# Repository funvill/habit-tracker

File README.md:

# Every DayCalendar - Single Month board - KiCad

A single month habit tracker inspired by [Simone Giertz “The Every Day Calendar”](https://www.kickstarter.com/projects/simonegiertz/the-every-day-calendar). Allows for tracking of stats for multiple activities throughout the year. On each day, click the buttons for the activities that you have accomplished and the corresponding date on the calendar will illuminate with RGB LEDs.

- Months will progress automatically.
- Several different "modes"
- Physical buttons with leads to be able to expand on the board out to a frame.
- Ability to connect the boards together

Uses a ESP32 to connect to the internet and backup the data from the boards.

Fabricated using JLPCB SMD placement services. Fully automated manufacturing.

More information about this project can be found on my blog [project page](https://blog.abluestar.com/projects/2022-monthly-habit-tracker/)

See [changelog](changelog.md) for full list of changes

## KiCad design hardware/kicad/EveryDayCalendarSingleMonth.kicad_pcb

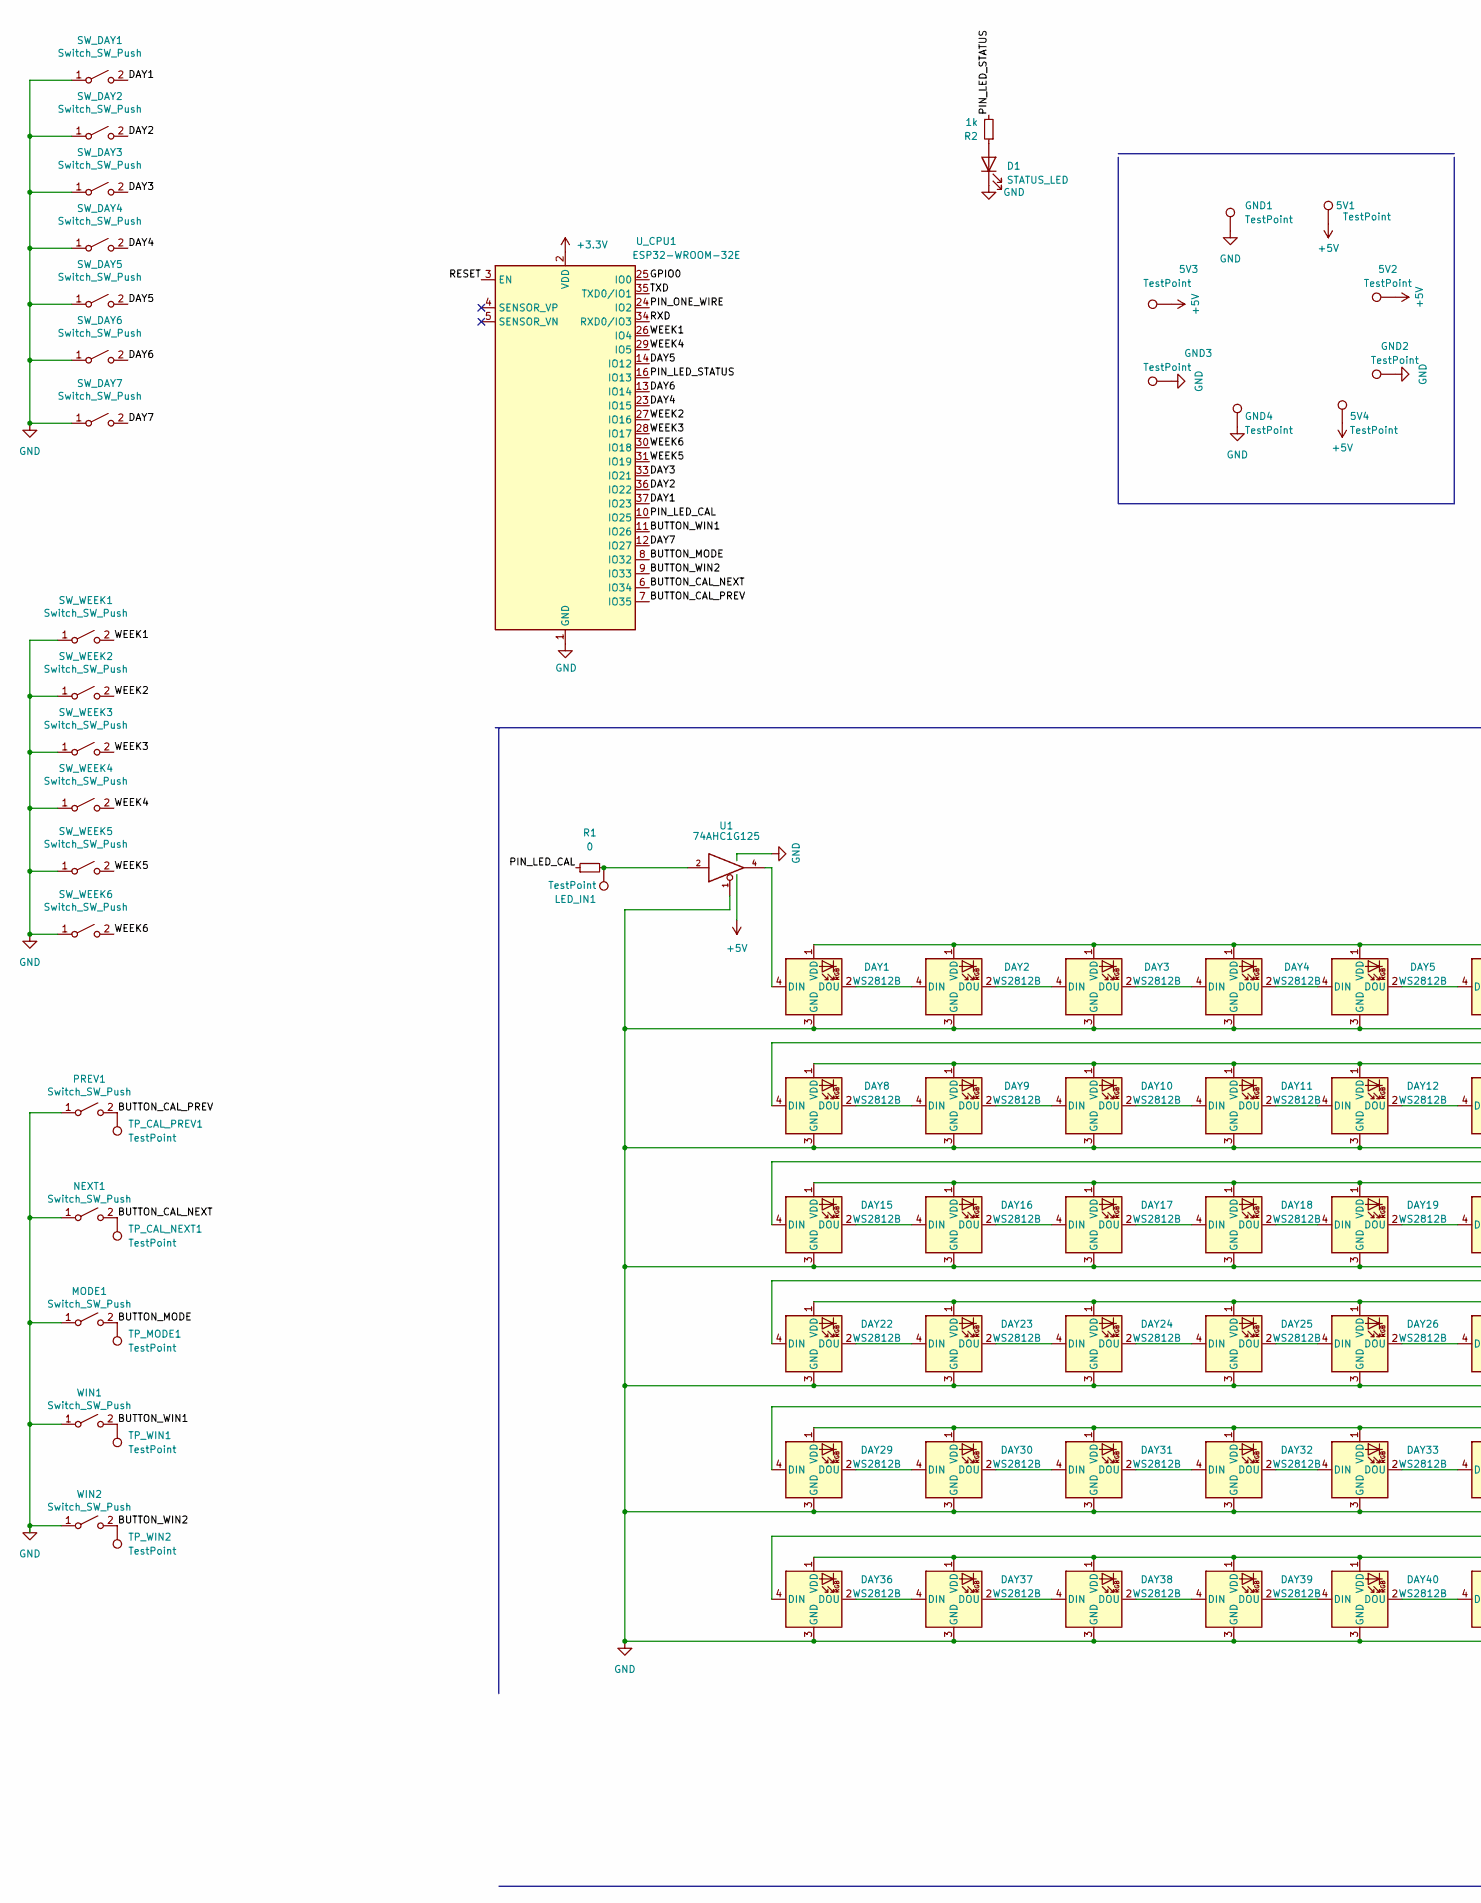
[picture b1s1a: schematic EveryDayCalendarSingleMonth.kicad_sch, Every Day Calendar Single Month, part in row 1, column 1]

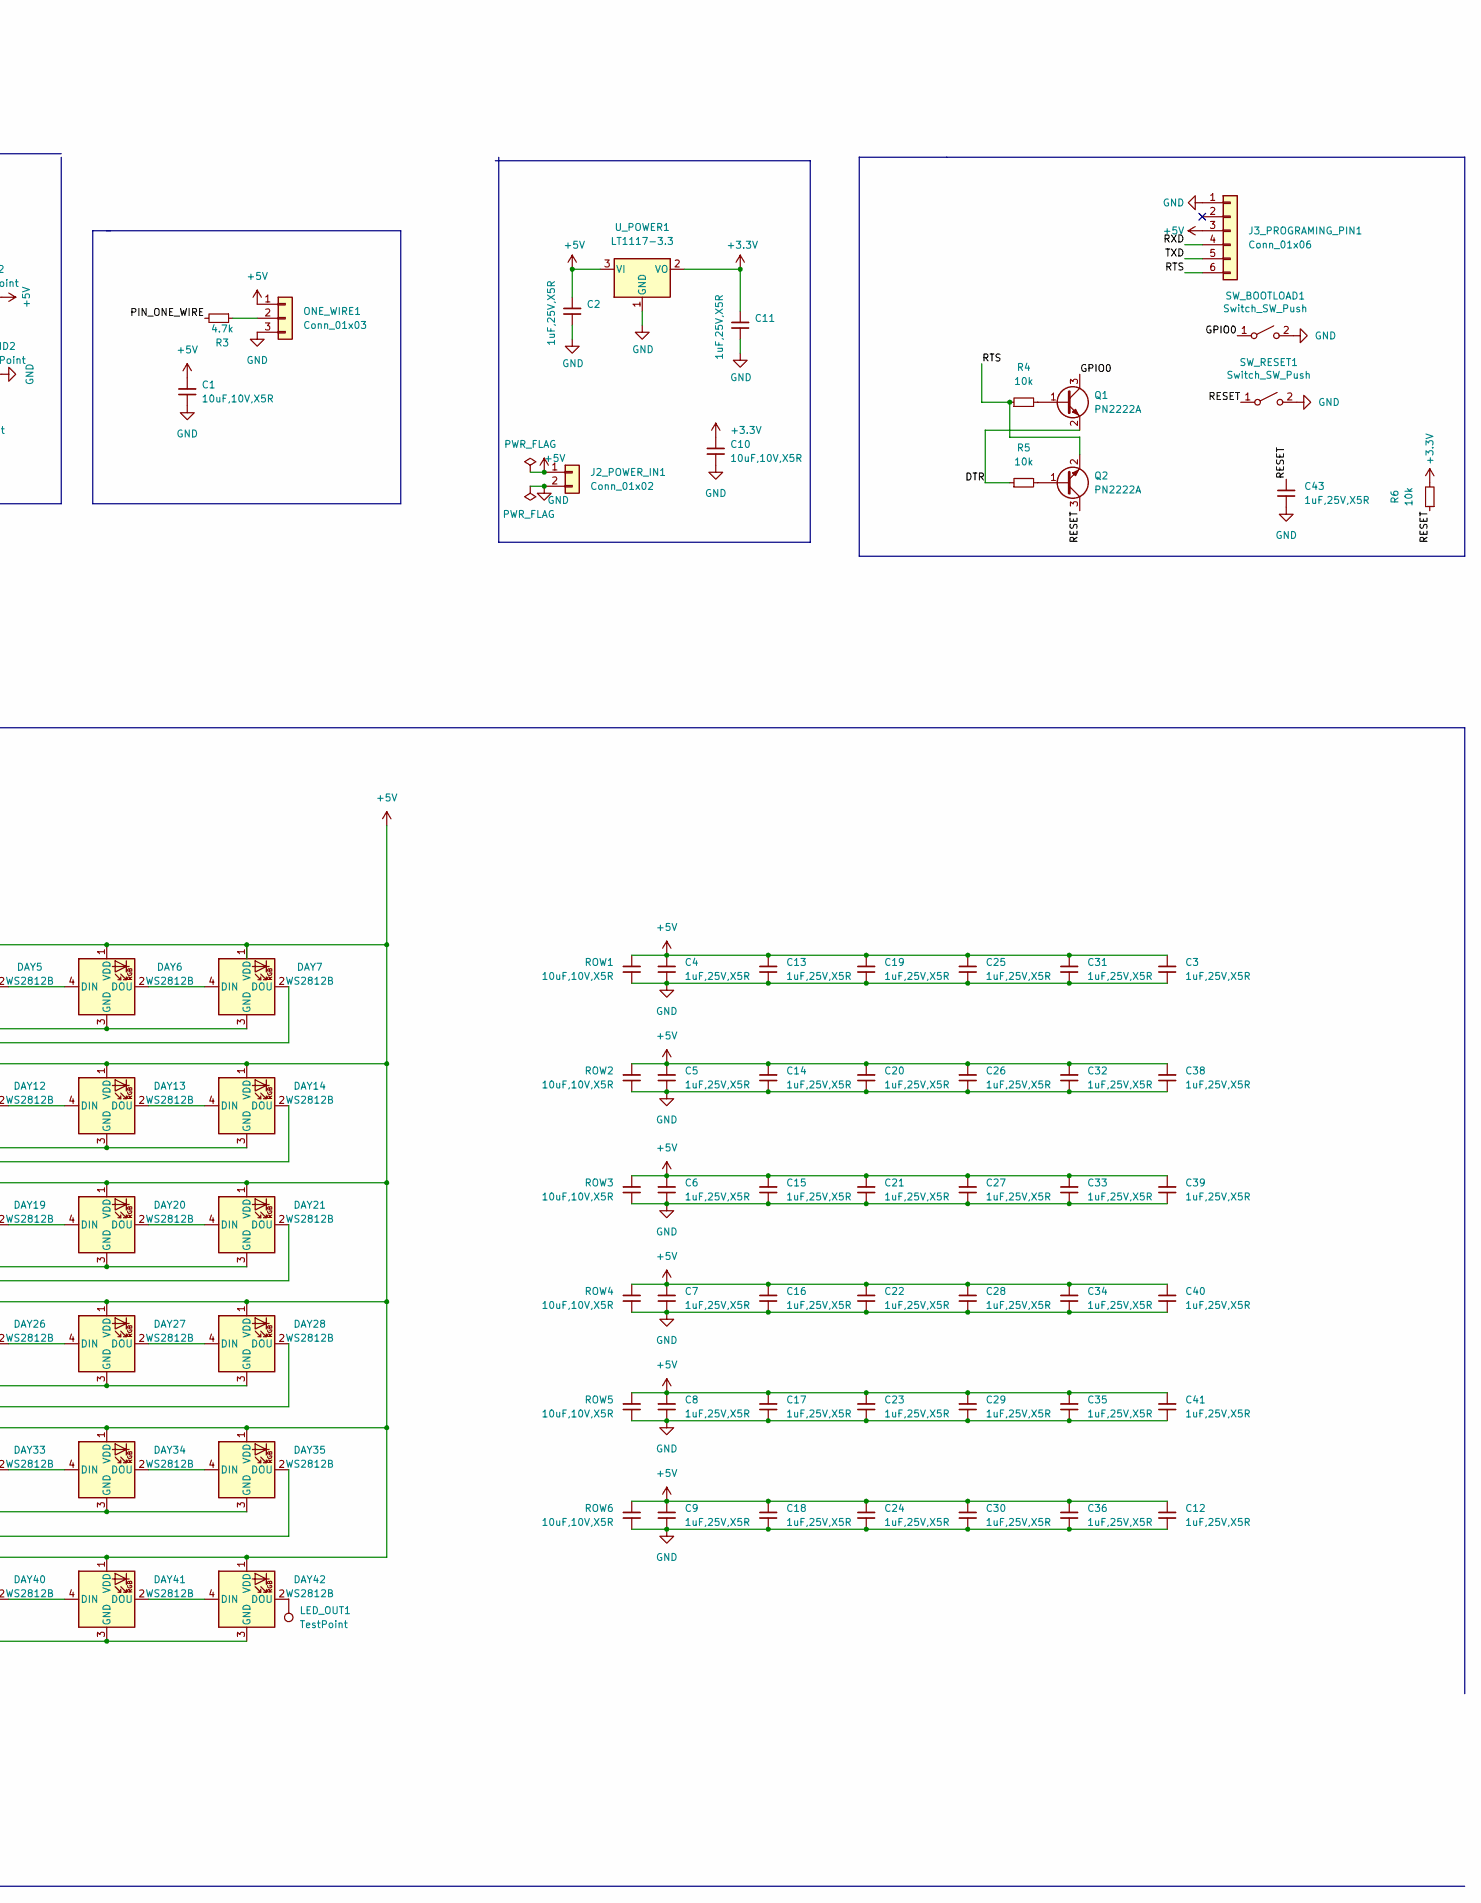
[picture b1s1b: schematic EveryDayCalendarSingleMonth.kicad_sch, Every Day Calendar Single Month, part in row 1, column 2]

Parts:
5V1, 5V2, 5V3, 5V4: TestPoint; TestPoint_Pad_2.5x2.5mm
C1, C10: 10uF,10V,X5R; C_0603_1608Metric; MFGPN CL10A106KP8NNNC; LCSC C19702
C2, C3, C4, C5, C6, C7, C8, C9, C11, C12, C13, C14, C15, C16, C17, C18, C19, C20, C21, C22, C23, C24, C25, C26, C27, C28, C29, C30, C31, C32, C33, C34, C35, C36, C38, C39, C40, C41, C43: 1uF,25V,X5R; C_0402_1005Metric; MFGPN CL05A105KA5NQNC; LCSC C52923
D1: STATUS_LED; LED_0603_1608Metric; LCSC C2286
DAY1, DAY2, DAY3, DAY4, DAY5, DAY6, DAY7, DAY8, DAY9, DAY10, DAY11, DAY12, DAY13, DAY14, DAY15, DAY16, DAY17, DAY18, DAY19, DAY20, DAY21, DAY22, DAY23, DAY24, DAY25, DAY26, DAY27, DAY28, DAY29, DAY30, DAY31, DAY32, DAY33, DAY34, DAY35, DAY36, DAY37, DAY38, DAY39, DAY40, DAY41, DAY42: WS2812B; LED_WS2812B_PLCC4_5.0x5.0mm_P3.2mm; LCSC C2843785
GND1, GND2, GND3, GND4: TestPoint; TestPoint_Pad_2.5x2.5mm
J2_POWER_IN1: Conn_01x02; PhoenixContact_MCV_1,5_2-G-3.81_1x02_P3.81mm_Vertical
J3_PROGRAMING_PIN1: Conn_01x06; PinHeader_1x06_P2.54mm_Vertical
LED_IN1: TestPoint; TestPoint_Pad_2.5x2.5mm
LED_OUT1: TestPoint; TestPoint_Pad_2.5x2.5mm
MODE1: Switch_SW_Push; SW_Push_1P1T_NO_6x6mm_H9.5mm; LCSC C221880
NEXT1: Switch_SW_Push; SW_Push_1P1T_NO_6x6mm_H9.5mm; LCSC C221880
ONE_WIRE1: Conn_01x03; PinHeader_1x03_P2.54mm_Vertical
PREV1: Switch_SW_Push; SW_Push_1P1T_NO_6x6mm_H9.5mm; LCSC C221880
Q1, Q2: PN2222A; SOT-416; LCSC C242260
R1: 0; R_0402_1005Metric; MFGPN 0402WGF0000TCE; LCSC C17168
R2: 1k; R_0402_1005Metric; MFGPN 0402WGF1001TCE; LCSC C11702
R3: 4.7k; R_0402_1005Metric; MFGPN 0402WGF4701TCE; LCSC C25900
R4, R5, R6: 10k; R_0402_1005Metric; MFGPN 0402WGF1002TCE; LCSC C25744
ROW1, ROW2, ROW3, ROW4, ROW5, ROW6: 10uF,10V,X5R; C_0603_1608Metric; MFGPN CL10A106KP8NNNC; LCSC C19702
SW_BOOTLOAD1: Switch_SW_Push; SW_Push_1P1T_NO_6x6mm_H9.5mm; LCSC DNP
SW_DAY1, SW_DAY2, SW_DAY3, SW_DAY4, SW_DAY5, SW_DAY6, SW_DAY7: Switch_SW_Push; SW_Push_1P1T_NO_6x6mm_H9.5mm; LCSC C221880
SW_RESET1: Switch_SW_Push; SW_Push_1P1T_NO_6x6mm_H9.5mm; LCSC DNP
SW_WEEK1, SW_WEEK2, SW_WEEK3, SW_WEEK4, SW_WEEK5, SW_WEEK6: Switch_SW_Push; SW_Push_1P1T_NO_6x6mm_H9.5mm; LCSC C221880
TP_CAL_NEXT1: TestPoint; TestPoint_Pad_2.5x2.5mm
TP_CAL_PREV1: TestPoint; TestPoint_Pad_2.5x2.5mm
TP_MODE1: TestPoint; TestPoint_Pad_2.5x2.5mm
TP_WIN1, TP_WIN2: TestPoint; TestPoint_Pad_2.5x2.5mm
U1: 74AHC1G125; SOT-23-5; LCSC C23654
U_CPU1: ESP32-WROOM-32E; ESP32-WROOM-32; LCSC C701342
U_POWER1: LT1117-3.3; TO-263-3_TabPin2; LCSC C498315
WIN1, WIN2: Switch_SW_Push; SW_Push_1P1T_NO_6x6mm_H9.5mm; LCSC C221880

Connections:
+3.3V: C10.1, C11.1, R6.2, U_CPU1.2 (VDD), U_POWER1.2 (VO)
+5V: 5V1.1, 5V2.1, 5V3.1, 5V4.1, C1.1, C2.1, C3.1, C4.1, C5.1, C6.1, C7.1, C8.1, C9.1, C12.1, C13.1, C14.1, C15.1, C16.1, C17.1, C18.1, C19.1, C20.1, C21.1, C22.1, C23.1, C24.1, C25.1, C26.1, C27.1, C28.1, C29.1, C30.1, C31.1, C32.1, C33.1, C34.1, C35.1, C36.1, C38.1, C39.1, C40.1, C41.1, DAY1.1 (VDD), DAY2.1 (VDD), DAY3.1 (VDD), DAY4.1 (VDD), DAY5.1 (VDD), DAY6.1 (VDD), DAY7.1 (VDD), DAY8.1 (VDD), DAY9.1 (VDD), DAY10.1 (VDD), DAY11.1 (VDD), DAY12.1 (VDD), DAY13.1 (VDD), DAY14.1 (VDD), DAY15.1 (VDD), DAY16.1 (VDD), DAY17.1 (VDD), DAY18.1 (VDD), DAY19.1 (VDD), DAY20.1 (VDD), DAY21.1 (VDD), DAY22.1 (VDD), DAY23.1 (VDD), DAY24.1 (VDD), DAY25.1 (VDD), DAY26.1 (VDD), DAY27.1 (VDD), DAY28.1 (VDD), DAY29.1 (VDD), DAY30.1 (VDD), DAY31.1 (VDD), DAY32.1 (VDD), DAY33.1 (VDD), DAY34.1 (VDD), DAY35.1 (VDD), DAY36.1 (VDD), DAY37.1 (VDD), DAY38.1 (VDD), DAY39.1 (VDD), DAY40.1 (VDD), DAY41.1 (VDD), DAY42.1 (VDD), J2_POWER_IN1.1, J3_PROGRAMING_PIN1.3, ONE_WIRE1.1, ROW1.2, ROW2.2, ROW3.2, ROW4.2, ROW5.2, ROW6.2, U1.5 (VCC), U_POWER1.3 (VI)
/BUTTON_CAL_NEXT: NEXT1.2 (B), TP_CAL_NEXT1.1, U_CPU1.6 (IO34)
/BUTTON_CAL_PREV: PREV1.2 (B), TP_CAL_PREV1.1, U_CPU1.7 (IO35)
/BUTTON_MODE: MODE1.2 (B), TP_MODE1.1, U_CPU1.8 (IO32)
/BUTTON_WIN1: TP_WIN1.1, U_CPU1.11 (IO26), WIN1.2 (B)
/BUTTON_WIN2: TP_WIN2.1, U_CPU1.9 (IO33), WIN2.2 (B)
/DAY1: SW_DAY1.2 (B), U_CPU1.37 (IO23)
/DAY2: SW_DAY2.2 (B), U_CPU1.36 (IO22)
/DAY3: SW_DAY3.2 (B), U_CPU1.33 (IO21)
/DAY4: SW_DAY4.2 (B), U_CPU1.23 (IO15)
/DAY5: SW_DAY5.2 (B), U_CPU1.14 (IO12)
/DAY6: SW_DAY6.2 (B), U_CPU1.13 (IO14)
/DAY7: SW_DAY7.2 (B), U_CPU1.12 (IO27)
/DTR: Q1.2 (E), R5.1
/GPIO0: Q1.3 (C), SW_BOOTLOAD1.1 (A), U_CPU1.25 (IO0)
/PIN_LED_CAL: R1.1, U_CPU1.10 (IO25)
/PIN_LED_STATUS: R2.2, U_CPU1.16 (IO13)
/PIN_ONE_WIRE: R3.2, U_CPU1.24 (IO2)
/RESET: C43.1, Q2.3 (C), R6.1, SW_RESET1.1 (A), U_CPU1.3 (EN)
/RTS: J3_PROGRAMING_PIN1.6, Q2.2 (E), R4.1
/RXD: J3_PROGRAMING_PIN1.4, U_CPU1.34 (RXD0/IO3)
/TXD: J3_PROGRAMING_PIN1.5, U_CPU1.35 (TXD0/IO1)
/WEEK1: SW_WEEK1.2 (B), U_CPU1.26 (IO4)
/WEEK2: SW_WEEK2.2 (B), U_CPU1.27 (IO16)
/WEEK3: SW_WEEK3.2 (B), U_CPU1.28 (IO17)
/WEEK4: SW_WEEK4.2 (B), U_CPU1.29 (IO5)
/WEEK5: SW_WEEK5.2 (B), U_CPU1.31 (IO19)
/WEEK6: SW_WEEK6.2 (B), U_CPU1.30 (IO18)
GND: C1.2, C2.2, C3.2, C4.2, C5.2, C6.2, C7.2, C8.2, C9.2, C10.2, C11.2, C12.2, C13.2, C14.2, C15.2, C16.2, C17.2, C18.2, C19.2, C20.2, C21.2, C22.2, C23.2, C24.2, C25.2, C26.2, C27.2, C28.2, C29.2, C30.2, C31.2, C32.2, C33.2, C34.2, C35.2, C36.2, C38.2, C39.2, C40.2, C41.2, C43.2, D1.1 (K), DAY1.3 (GND), DAY2.3 (GND), DAY3.3 (GND), DAY4.3 (GND), DAY5.3 (GND), DAY6.3 (GND), DAY7.3 (GND), DAY8.3 (GND), DAY9.3 (GND), DAY10.3 (GND), DAY11.3 (GND), DAY12.3 (GND), DAY13.3 (GND), DAY14.3 (GND), DAY15.3 (GND), DAY16.3 (GND), DAY17.3 (GND), DAY18.3 (GND), DAY19.3 (GND), DAY20.3 (GND), DAY21.3 (GND), DAY22.3 (GND), DAY23.3 (GND), DAY24.3 (GND), DAY25.3 (GND), DAY26.3 (GND), DAY27.3 (GND), DAY28.3 (GND), DAY29.3 (GND), DAY30.3 (GND), DAY31.3 (GND), DAY32.3 (GND), DAY33.3 (GND), DAY34.3 (GND), DAY35.3 (GND), DAY36.3 (GND), DAY37.3 (GND), DAY38.3 (GND), DAY39.3 (GND), DAY40.3 (GND), DAY41.3 (GND), DAY42.3 (GND), GND1.1, GND2.1, GND3.1, GND4.1, J2_POWER_IN1.2, J3_PROGRAMING_PIN1.1, MODE1.1 (A), NEXT1.1 (A), ONE_WIRE1.3, PREV1.1 (A), ROW1.1, ROW2.1, ROW3.1, ROW4.1, ROW5.1, ROW6.1, SW_BOOTLOAD1.2 (B), SW_DAY1.1 (A), SW_DAY2.1 (A), SW_DAY3.1 (A), SW_DAY4.1 (A), SW_DAY5.1 (A), SW_DAY6.1 (A), SW_DAY7.1 (A), SW_RESET1.2 (B), SW_WEEK1.1 (A), SW_WEEK2.1 (A), SW_WEEK3.1 (A), SW_WEEK4.1 (A), SW_WEEK5.1 (A), SW_WEEK6.1 (A), U1.1, U1.3 (GND), U_CPU1.1 (GND), U_CPU1.15 (GND), U_CPU1.38 (GND), U_CPU1.39 (GND), U_POWER1.1 (GND), WIN1.1 (A), WIN2.1 (A)
unnamed: D1.2 (A), R2.1
unnamed: DAY1.2 (DOU), DAY2.4 (DIN)
unnamed: DAY1.4 (DIN), U1.4
unnamed: DAY2.2 (DOU), DAY3.4 (DIN)
unnamed: DAY3.2 (DOU), DAY4.4 (DIN)
unnamed: DAY4.2 (DOU), DAY5.4 (DIN)
unnamed: DAY5.2 (DOU), DAY6.4 (DIN)
unnamed: DAY6.2 (DOU), DAY7.4 (DIN)
unnamed: DAY7.2 (DOU), DAY8.4 (DIN)
unnamed: DAY8.2 (DOU), DAY9.4 (DIN)
unnamed: DAY10.2 (DOU), DAY11.4 (DIN)
unnamed: DAY9.2 (DOU), DAY10.4 (DIN)
unnamed: DAY11.2 (DOU), DAY12.4 (DIN)
unnamed: DAY12.2 (DOU), DAY13.4 (DIN)
unnamed: DAY13.2 (DOU), DAY14.4 (DIN)
unnamed: DAY14.2 (DOU), DAY15.4 (DIN)
unnamed: DAY15.2 (DOU), DAY16.4 (DIN)
unnamed: DAY16.2 (DOU), DAY17.4 (DIN)
unnamed: DAY17.2 (DOU), DAY18.4 (DIN)
unnamed: DAY18.2 (DOU), DAY19.4 (DIN)
unnamed: DAY19.2 (DOU), DAY20.4 (DIN)
unnamed: DAY20.2 (DOU), DAY21.4 (DIN)
unnamed: DAY21.2 (DOU), DAY22.4 (DIN)
unnamed: DAY22.2 (DOU), DAY23.4 (DIN)
unnamed: DAY23.2 (DOU), DAY24.4 (DIN)
unnamed: DAY24.2 (DOU), DAY25.4 (DIN)
unnamed: DAY25.2 (DOU), DAY26.4 (DIN)
unnamed: DAY26.2 (DOU), DAY27.4 (DIN)
unnamed: DAY27.2 (DOU), DAY28.4 (DIN)
unnamed: DAY28.2 (DOU), DAY29.4 (DIN)
unnamed: DAY29.2 (DOU), DAY30.4 (DIN)
unnamed: DAY30.2 (DOU), DAY31.4 (DIN)
unnamed: DAY31.2 (DOU), DAY32.4 (DIN)
unnamed: DAY32.2 (DOU), DAY33.4 (DIN)
unnamed: DAY33.2 (DOU), DAY34.4 (DIN)
unnamed: DAY34.2 (DOU), DAY35.4 (DIN)
unnamed: DAY35.2 (DOU), DAY36.4 (DIN)
unnamed: DAY36.2 (DOU), DAY37.4 (DIN)
unnamed: DAY37.2 (DOU), DAY38.4 (DIN)
unnamed: DAY38.2 (DOU), DAY39.4 (DIN)
unnamed: DAY39.2 (DOU), DAY40.4 (DIN)
unnamed: DAY40.2 (DOU), DAY41.4 (DIN)
unnamed: DAY41.2 (DOU), DAY42.4 (DIN)
unnamed: DAY42.2 (DOU), LED_OUT1.1
unnamed: LED_IN1.1, R1.2, U1.2
unnamed: ONE_WIRE1.2, R3.1
unnamed: Q1.1 (B), R4.2
unnamed: Q2.1 (B), R5.2

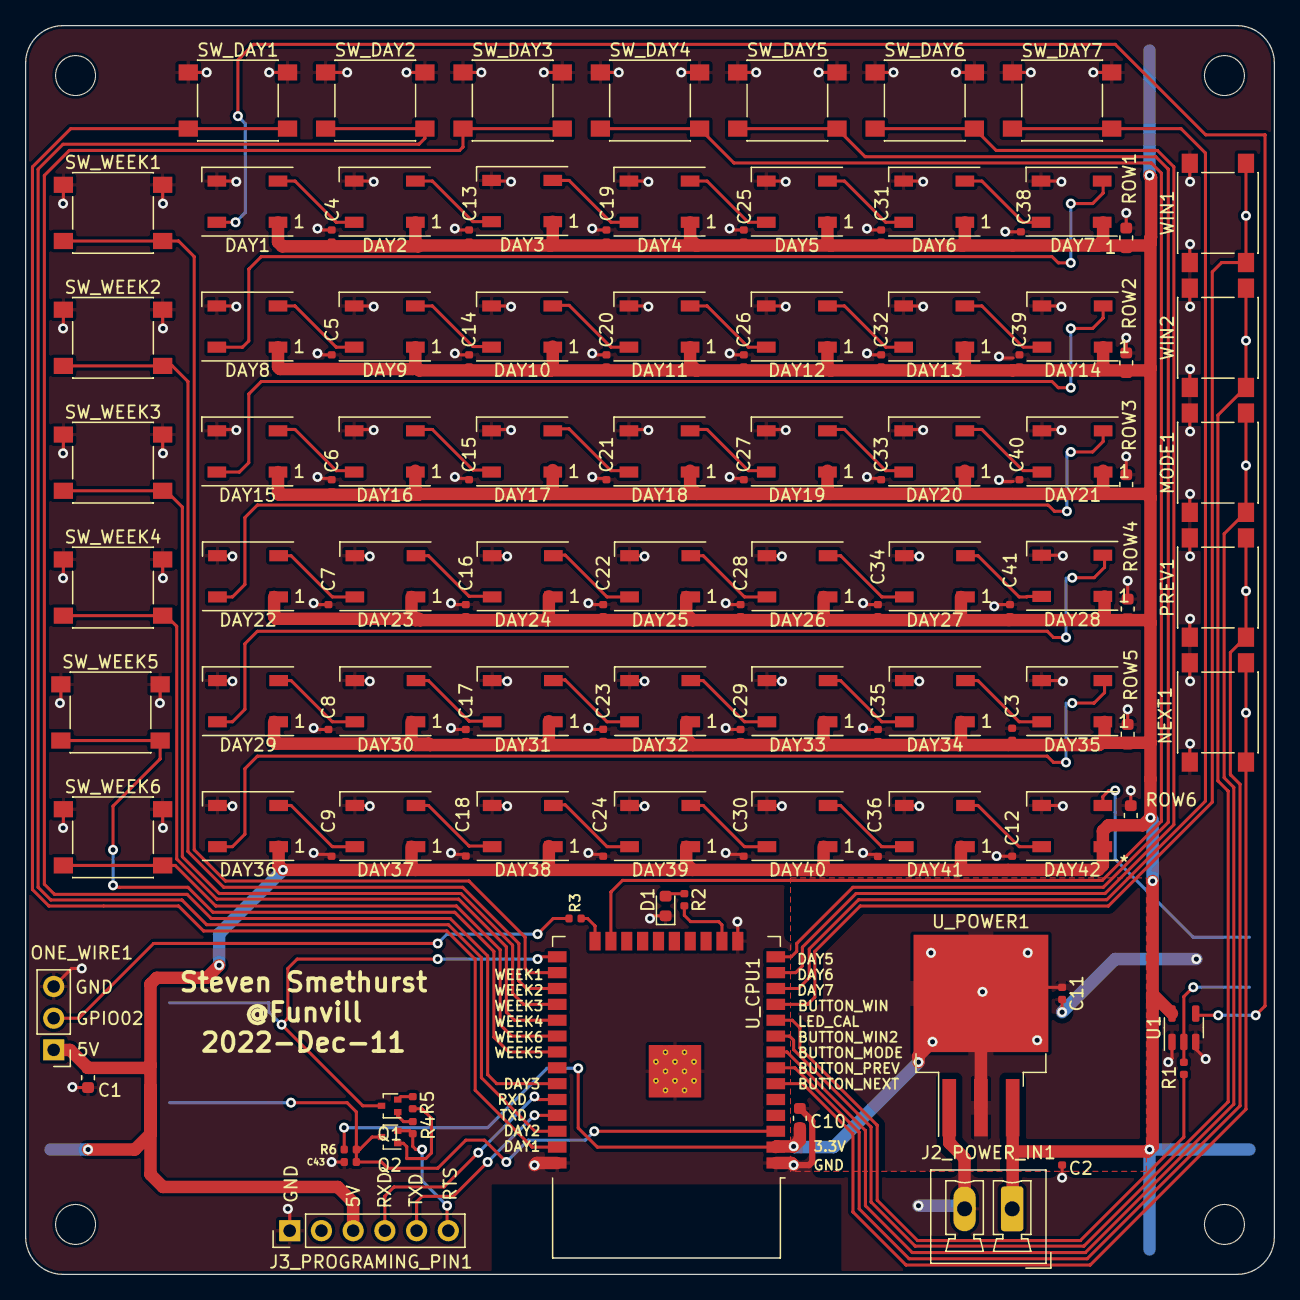
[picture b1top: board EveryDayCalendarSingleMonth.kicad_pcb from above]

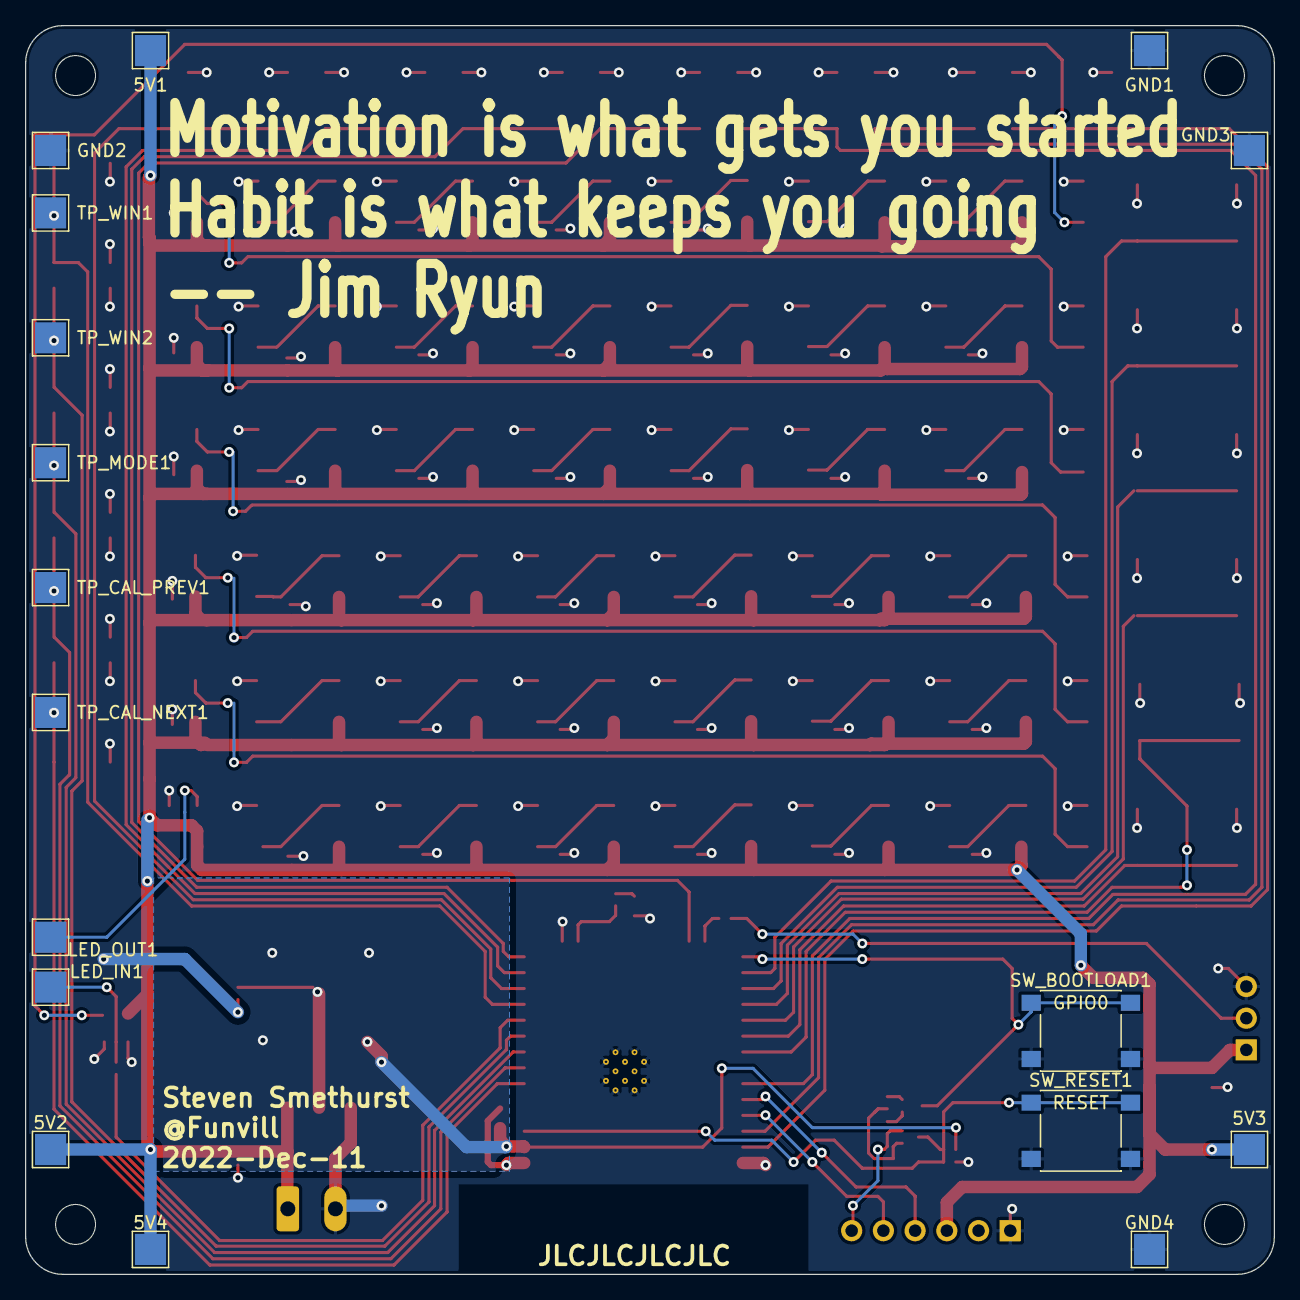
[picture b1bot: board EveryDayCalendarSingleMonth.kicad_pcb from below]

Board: 2 copper layers, 100.0 x 100.0 mm, 143 parts (17 on the bottom side), 78 nets.

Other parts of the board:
TP_CORNER_1, TP_CORNER_2, TP_CORNER_3, TP_CORNER_4: TestPoint; MountingHole_3.2mm_M3

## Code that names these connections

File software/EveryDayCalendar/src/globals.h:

/**
 * Globals
 * A list of global variables and constants used in the project
 * Multiple files will include this file
 *
 */

#include <Arduino.h> // Required for ESP32
#include "FastLED.h" // Required for CHSV


#ifndef __GLOBAL_H__
#define __GLOBAL_H__

// The build version is shown on the loading screen.
// the version is shown in the serial prompt and the web page.
const uint8_t BUILD_NUMBER = 8;

// HTTP
#define HTTP_PORT 80

// Pins
// ESP32 Pins
// https://docs.espressif.com/projects/esp-idf/en/latest/esp32/api-reference/peripherals/gpio.html
const int PIN_WEEK1 = 4;   // IO-4  or pin 26
const int PIN_WEEK2 = 16;  // IO-16 or pin 27
const int PIN_WEEK3 = 17;  // IO-17 or pin 28
const int PIN_WEEK4 = 5;   // IO-5  or pin 29
const int PIN_WEEK5 = 19;  // IO-19 or pin 31
const int PIN_WEEK6 = 18;  // IO-18 or pin 30
const int PIN_DAY1 = 23;   // IO-23 or pin 37
const int PIN_DAY2 = 22;   // IO-22 or pin 36
const int PIN_DAY3 = 21;   // IO-21 or pin 33
const int PIN_DAY4 = 15;   // IO-15 or pin 23
const int PIN_DAY5 = 12;   // IO-12 or pin 14
const int PIN_DAY6 = 14;   // IO-14 or pin 13
const int PIN_DAY7 = 27;   // IO-27 or pin 12, GPIO27, ADC2_CH7, TOUCH7, RTC_GPIO17, EMAC_RX_DV
const int PIN_WIN1 = 26;   // IO-26 or pin 11
const int PIN_WIN2 = 33;   // IO-33 or pin  9
const int PIN_MODE = 32;   // IO-32 or pin  8
const int PIN_NEXT = 34;   // IO-34 or pin  6, Shares pins with U0RXD (serial). If serial is active you can't use thse pins
const int PIN_PREV = 35;   // IO-35 or pin  7, Shares pins with U0TXD (serial)
const int PIN_ONEWIRE = 2; // IO-0 or pin 24

const int PIN_LED_CALENDAR = 25; // IO-25 or pin 10
const int PIN_LED_STATUS = 13;   // IO-13 or pin 16

// Helpful for debugging when identifiying
// The actual LED on the matrix that is being addressed
const uint8_t DAY1 = 0;
const uint8_t DAY2 = 1;
const uint8_t DAY3 = 2;
const uint8_t DAY4 = 3;
const uint8_t DAY5 = 4;
const uint8_t DAY6 = 5;
const uint8_t DAY7 = 6;
const uint8_t DAY8 = 7;
const uint8_t DAY9 = 8;
const uint8_t DAY10 = 9;
const uint8_t DAY11 = 10;
const uint8_t DAY12 = 11;
const uint8_t DAY13 = 12;
const uint8_t DAY14 = 13;
const uint8_t DAY15 = 14;
const uint8_t DAY16 = 15;
const uint8_t DAY17 = 16;
const uint8_t DAY18 = 17;
const uint8_t DAY19 = 18;
const uint8_t DAY20 = 19;
const uint8_t DAY21 = 20;
const uint8_t DAY22 = 21;
const uint8_t DAY23 = 22;
const uint8_t DAY24 = 23;
const uint8_t DAY25 = 24;
const uint8_t DAY26 = 25;
const uint8_t DAY27 = 26;
const uint8_t DAY28 = 27;
const uint8_t DAY29 = 28;
const uint8_t DAY30 = 29;
const uint8_t DAY31 = 30;
const uint8_t DAY32 = 31;
const uint8_t DAY33 = 32;
const uint8_t DAY34 = 33;
const uint8_t DAY35 = 34;
const uint8_t DAY36 = 35;
const uint8_t DAY37 = 36;
const uint8_t DAY38 = 37;
const uint8_t DAY39 = 38;
const uint8_t DAY40 = 39;
const uint8_t DAY41 = 40;
const uint8_t DAY42 = 41;

// Modes
const uint8_t MODE_CALENDAR = 0;
const uint8_t MODE_BINARY_CLOCK = 1;
const uint8_t MODE_EPOCH_CLOCK = 2;
const uint8_t MODE_BREATHING = 3;
const uint8_t MODE_FADE_POINTS = 4;

const uint8_t MODE_START = MODE_FADE_POINTS;
const uint8_t MODE_MIN = MODE_CALENDAR;
const uint8_t MODE_MAX = MODE_FADE_POINTS;

// LED colors
// https://github.com/FastLED/FastLED/wiki/Pixel-reference
const CHSV COLOR_OFF = CHSV(0, 0, 0);          // Black
const CHSV COLOR_SUCCESS = CHSV(96, 255, 200); // Green
const CHSV COLOR_FAIL = CHSV(0, 255, 128);     // RED
const CHSV COLOR_FUTURE = CHSV(128, 255, 128); // Aqua
const CHSV COLOR_NOT_IN_MONTH = COLOR_OFF;     // Black
const CRGB COLOR_CURSOR = CRGB::Gold;
const CHSV COLOR_FONT = COLOR_SUCCESS;

const uint8_t LED_MATRIX_WIDTH = 7;
const uint8_t LED_MATRIX_HEIGHT = 6;

#define DAYS_IN_YEAR 365

const int timeZone = -8; // Pacific Standard Time (USA)
const long utcOffsetInSeconds = timeZone * 60 * 60;

static const char *MONTHS_SHORT[] = {"XXX", "Jan", "Feb", "Mar", "Apr", "May", "Jun", "Jul", "Aug", "Sep", "Oct", "Nov", "Dec"};

// 0 = Sunday, 1 = Monday, 2 = Tuesday, 3 = Wednesday, 4 = Thursday, 5 = Friday, 6 = Saturday,
static const char *DAY_SHORT[] = {"Sun", "Mon", "Tue", "Wen", "Thu", "Fri", "Sat"};

// Settings
// ------------------------------------------------------------
const uint8_t PIXELS_COUNT = LED_MATRIX_WIDTH * LED_MATRIX_HEIGHT; // 7x6
const uint8_t LED_BRIGHTNESS = 64;                                 // 0 DARK - 255 BRIGHT
const ulong FRAMES_PER_SECOND = 120;
const uint32_t BAUD_RATE = 115200;

// Globals
// ------------------------------------------------------------
// NeoPixel
extern CRGB leds[PIXELS_COUNT];


static uint8_t gMode;
static uint16_t gCurrentYear;
static uint8_t gCurrentMonth;

#endif // __GLOBAL_H__

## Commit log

2022-11-28 WIP PCB Schematic
2022-12-04 Move from RP2040 to ESP32, schematic mostly complete
2022-12-05 Schematic complete, pcb outline in place
2022-12-05 First step in PCB layout, getting everything sorted into their general locations
2022-12-05 Working on getting all the traces done
2022-12-06 added GND base
2022-12-06 Added 3d part for pushbuttons
2022-12-06 Zero errors or warnings.
2022-12-06 Updated silkscreen
2022-12-06 Updated the schematic from PCB layout with updated silkscreen
2022-12-06 Fussing with the tracks, no real change
2022-12-07 Keep optimizing the tracks
2022-12-07 Added gerber files
2022-12-07 added BOM
2022-12-11 As submitted to jlcpcb on Dec 10, 2022
2022-12-12 Restored from backups after bad merge
2022-12-12 As submitted to JLPCB on 11-Dec-2022
2022-12-12 Moved the LEDs slightly and resubmitted to JLPCB
2022-12-12 Added readme
2022-12-27 WIP: Testing the hardware and setting up the display
2022-12-27 WIP: Database loaded and saved to eeprom
2022-12-28 WIP: Separated the code into multiple files to clean it up
2022-12-28 Captative portal and OTA updates.
2022-12-28 SSID and Password updates from Captive portal
2022-12-28 Removed hardcoded SSIDs from source code
2022-12-29 Adding scrolling font
2022-12-29 Added numbers and letters to the font
2022-12-29 Next and Prev month buttons
2022-12-29 Build 1 ready for beta customer
2022-12-29 Added photo of the hardware
2023-01-04 Moved modes to their own files, Added a fades pixel animation, Added reset wifi command
2023-01-09 Added laser cut files for the top plate, separator, and back plate
2023-01-12 Automatic builds on push
2023-01-12 tab issue
2023-01-12 Added lib_ldf_mode = deep+
2023-01-12 lowercase t in time.h
2023-01-12 Added hardcoded firmware.json file to public folder
2023-01-12 Github pages
2023-01-12 Moved the firmware.json to the docs folder
2023-01-12 Testing esp32FOTA version 0.0.5
2023-01-12 With auto update via a firmware on github page
2023-01-16 version 6
    ## 2023-Jan-08 (build 6)
    - Save the month, year, and mode to eeprom on change
    - Randomized seed on startup based on wifi noise
    ## 2023-Jan-08 (build 3-5)
    - Added ability to update via Github
2023-01-16 Update version number to "6"
2023-01-16 If year is corrupted then reset year to 2023 (build 7)
2023-01-16 Update animation
2023-01-16 Fixed issue where mode was not being saved between power cycles (build 8)
    ## 2023-Jan-08 (build 8)
    - Fixed issue where mode was not being saved between power cycles
